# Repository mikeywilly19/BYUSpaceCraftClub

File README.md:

# BYUSpaceCraftClub

Files for PocketQube project

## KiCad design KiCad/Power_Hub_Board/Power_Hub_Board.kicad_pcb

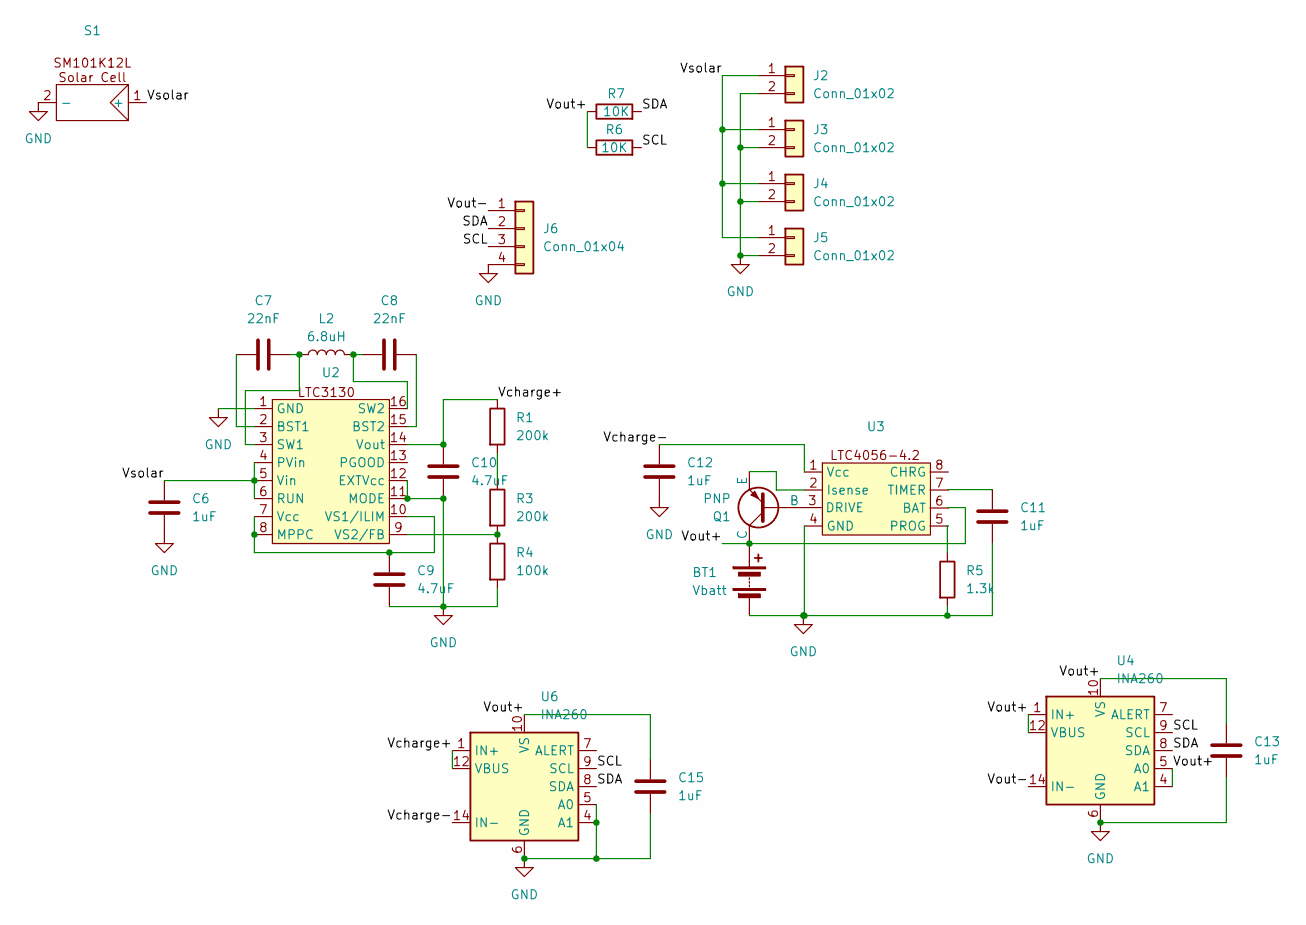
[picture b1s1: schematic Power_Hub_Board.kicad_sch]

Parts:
BT1: Vbatt; Molex_PicoBlade_53398-0271_1x02-1MP_P1.25mm_Vertical; MPN C122410
C6, C11, C12, C13, C15: 1uF; C_0603_1608Metric; MPN C59302
C7, C8: 22nF; C_0603_1608Metric; MPN C77571
C9, C10: 4.7uF; C_0603_1608Metric; MPN C69182
J2, J3, J4, J5: Conn_01x02; Molex_PicoBlade_53398-0271_1x02-1MP_P1.25mm_Vertical; MPN C122410
J6: Conn_01x04; Molex_PicoBlade_53398-0471_1x04-1MP_P1.25mm_Vertical; MPN C234195
L2: 6.8uH; L_1206_3216Metric; MPN C3223943
Q1: PNP; SOT-23; MPN C2147
R1, R3: 200k; R_0402_1005Metric; MPN C25764
R4: 100k; R_0402_1005Metric; MPN C25530
R5: 1.3k; R_0402_1005Metric; MPN C25866
R6, R7: 10K; R_0402_1005Metric; MPN C25531
S1: SM101K12L
U2: MSOP-16-1EP_3x4.039mm_P0.5mm_EP1.651x2.845mm_ThermalVias; MPN C684231
U3: TSOT-23-8_HandSoldering; MPN C687184
U4, U6: INA260; TSSOP-16_4.4x5mm_P0.65mm; MPN C2155885

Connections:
/SCL: J6.3, R6.2, U4.9 (SCL), U6.9 (SCL)
/SDA: J6.2, R7.2, U4.8 (SDA), U6.8 (SDA)
/Vcharge+: C10.1, R1.1, U2.14 (Vout), U6.1 (IN+), U6.2 (IN+), U6.3 (IN+), U6.12 (VBUS)
/Vcharge-: C12.1, U3.1 (Vcc), U6.14 (IN-), U6.15 (IN-), U6.16 (IN-)
/Vout+: BT1.1 (+), C13.1, C15.1, Q1.1 (C), R6.1, R7.1, U3.6 (BAT), U4.1 (IN+), U4.2 (IN+), U4.3 (IN+), U4.4 (A1), U4.5 (A0), U4.10 (VS), U4.12 (VBUS), U6.10 (VS)
/Vout-: J6.1, U4.14 (IN-), U4.15 (IN-), U4.16 (IN-)
/Vsolar: C6.2, J2.1, J3.1, J4.1, J5.1, S1.1 (+), U2.4 (PVin), U2.5 (Vin), U2.6 (RUN)
GND: BT1.2 (-), C6.1, C9.1, C10.2, C11.2, C12.2, C13.2, C15.2, J2.2, J3.2, J4.2, J5.2, J6.4, R4.2, R5.2, S1.2 (-), U2.1 (GND), U2.11 (MODE), U2.12 (EXTVcc), U3.4 (GND), U4.6 (GND), U4.11 (GND), U6.4 (A1), U6.5 (A0), U6.6 (GND), U6.11 (GND)
unnamed: Q1.2 (B), U3.3 (DRIVE)
unnamed: Q1.3 (E), U3.2 (Isense)
unnamed: R1.2, R3.1
unnamed: C7.1, U2.2 (BST1)
unnamed: C8.2, U2.15 (BST2)
unnamed: C9.2, U2.7 (Vcc), U2.8 (MPPC), U2.10 (VS1/ILIM)
unnamed: C7.2, L2.1, U2.3 (SW1)
unnamed: C8.1, L2.2, U2.16 (SW2)
unnamed: R3.2, R4.1, U2.9 (VS2/FB)
unnamed: R5.1, U3.5 (PROG)
unnamed: C11.1, U3.7 (TIMER)

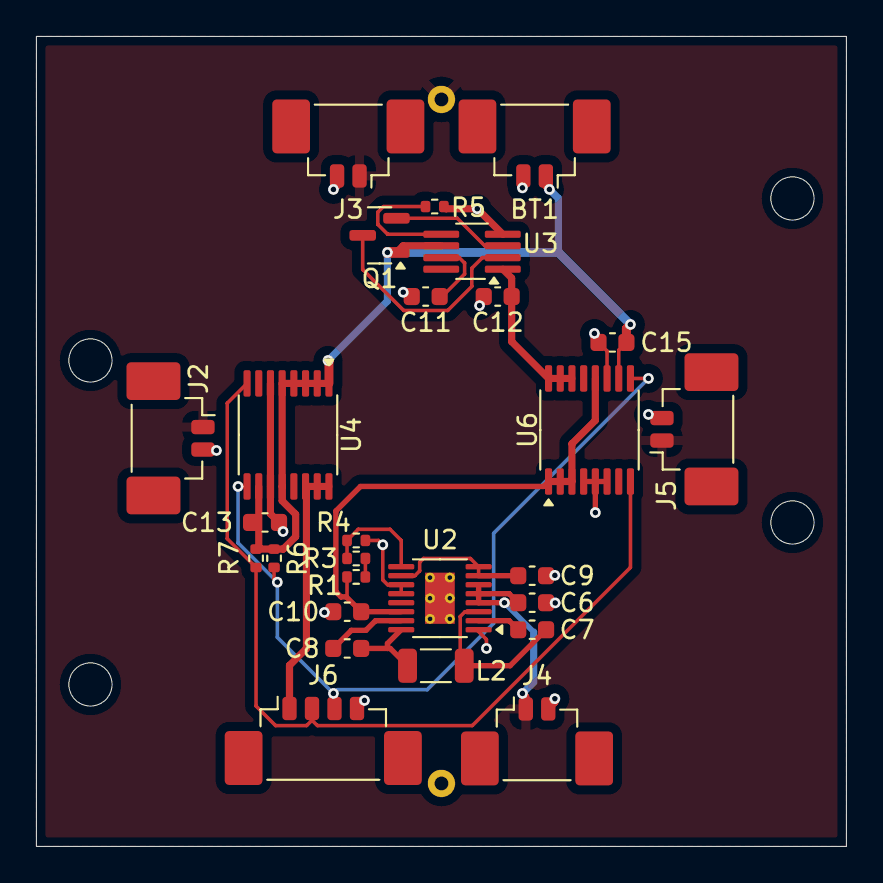
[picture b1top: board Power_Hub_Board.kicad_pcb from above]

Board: 2 copper layers, 45.0 x 45.0 mm, 28 parts (1 on the bottom side), 19 nets.

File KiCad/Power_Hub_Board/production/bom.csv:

Designator,Footprint,Quantity,Value,LCSC Part #
BT1,Molex_PicoBlade_53398-0271_1x02-1MP_P1.25mm_Vertical,1,Vbatt,C122410
"C10, C9",0603,2,4.7uF,C69182
"C11, C12, C13, C15, C6",0603,5,1uF,C59302
"C7, C8",0603,2,22nF,C77571
"J2, J3, J4, J5",Molex_PicoBlade_53398-0271_1x02-1MP_P1.25mm_Vertical,4,Conn_01x02,C122410
J6,Molex_PicoBlade_53398-0471_1x04-1MP_P1.25mm_Vertical,1,Conn_01x04,C234195
L2,1206,1,6.8uH,C3223943
Q1,SOT-23,1,PNP,C2147
"R1, R3",0402,2,200k,C25764
R4,0402,1,100k,C25530
R5,0402,1,1.3k,C25866
"R6, R7",0402,2,10K,C25531
U2,MSOP-16-1EP_3x4.039mm_P0.5mm_EP1.651x2.845mm_ThermalVias,1,~,C684231
U3,TSOT-23-8_HandSoldering,1,~,C687184
"U4, U6",TSSOP-16_4.4x5mm_P0.65mm,2,INA260,C2155885

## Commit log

2022-09-20 Moved files to new directory
2023-02-17 Edits to power pcb
2023-02-17 Added files for weather ballon test on SAMD21
2023-02-20 ArduCam libraries to WB-test
2023-02-21 added Libraries for Adafruit sensor and IO bus also changed camera test Main.cpp to the full function example code
2023-02-21 Adafruit sensor added to new directory
2023-02-22 Adafruit BME library added
2023-02-22 Adafruit BUS IO
2023-02-23 Edited libraries to fix calling issues
2023-02-23 Added test for SD card reading/writing etc
2023-02-26 Changed pin #'s to match new circuit
2023-03-01 Update test code for new test board
2023-03-01 testing Alitmeter
2023-03-01 Base code is added not sure if it works due to some interaction between the SD card and the camera on spi
2023-03-15 working camera writing to SD card
2023-03-15 minor changes for pin placement
2023-03-20 Added code from camera branch to set up camera and take images
2023-03-22 with '#' will be ignored, and an empty message aborts the commit.
2023-03-22 BME test created
2023-03-29 Added FSM branch
2023-03-29 added stuff to the state machine to improve
2023-04-04 Finished the code for the PCB
2023-04-05 Added code for radio transmission
2023-04-07 Added Radio test file
2023-04-12 added additional documentation
2025-03-19 power pcb
